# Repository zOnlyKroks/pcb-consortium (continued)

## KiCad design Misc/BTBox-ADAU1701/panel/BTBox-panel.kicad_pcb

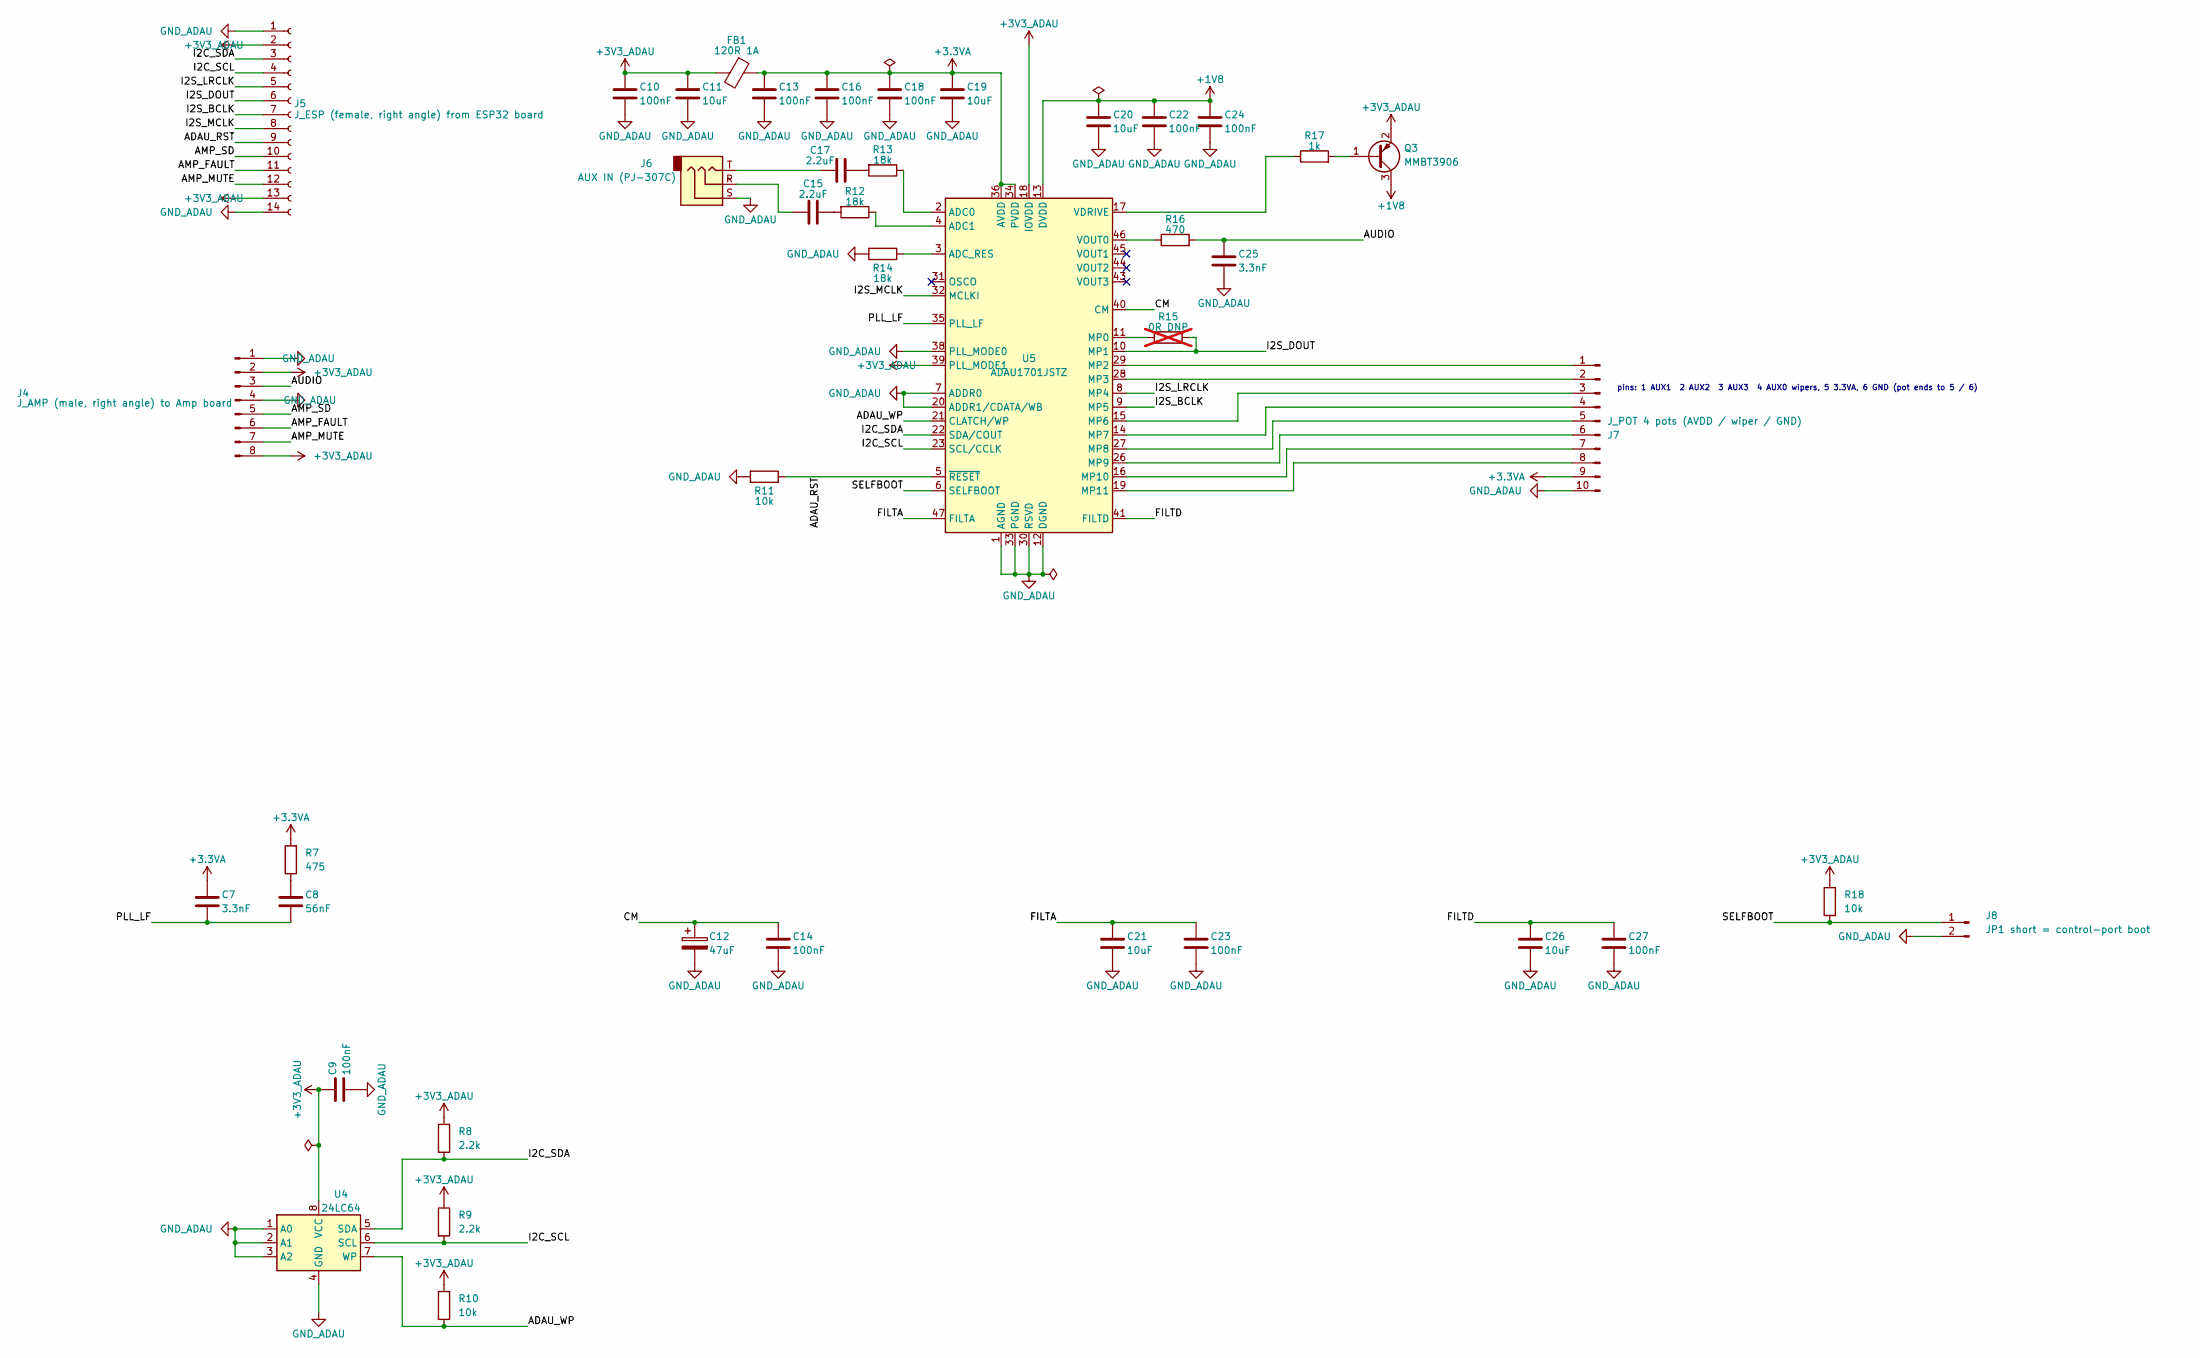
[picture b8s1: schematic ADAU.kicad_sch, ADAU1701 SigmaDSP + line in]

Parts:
C7, C25: 3.3nF; C_0603_1608Metric; LCSC Part # C1613
C8: 56nF; C_0603_1608Metric; LCSC Part # C282072
C9, C10, C13, C14, C16, C18, C22, C23, C24, C27: 100nF; C_0603_1608Metric; LCSC Part # C14663
C11, C19, C20, C21, C26: 10uF; C_0805_2012Metric; LCSC Part # C15850
C12: 47uF; CP_Elec_6.3x5.4; LCSC Part # C7469965
C15, C17: 2.2uF; C_0805_2012Metric; LCSC Part # C19110
FB1: 120R 1A; L_0805_2012Metric; LCSC Part # C356986
J4: J_AMP (male, right angle) to Amp board; PinHeader_1x08_P2.54mm_Horizontal
J5: J_ESP (female, right angle) from ESP32 board; PinSocket_1x14_P2.54mm_Horizontal
J6: AUX IN (PJ-307C); AUDIO-TH_PJ307C; LCSC Part # C16684
J7: J_POT 4 pots (AVDD / wiper / GND); PinSocket_1x10_P2.54mm_Vertical
J8: JP1 short = control-port boot; PinHeader_1x02_P2.54mm_Vertical; LCSC Part # C2894925
Q3: MMBT3906; SOT-23; LCSC Part # C53444
R7: 475; R_0603_1608Metric; LCSC Part # C23181
R8, R9: 2.2k; R_0603_1608Metric; LCSC Part # C4190
R10, R11, R18: 10k; R_0603_1608Metric; LCSC Part # C25804
R12, R13, R14: 18k; R_0603_1608Metric; LCSC Part # C100821
R15: 0R DNP; R_0603_1608Metric; LCSC Part # C21189; not fitted
R16: 470; R_0603_1608Metric; LCSC Part # C23179
R17: 1k; R_0603_1608Metric; LCSC Part # C21190
U4: 24LC64; SOIC-8_3.9x4.9mm_P1.27mm; LCSC Part # C5460
U5: ADAU1701JSTZ; LQFP-48_7x7mm_P0.5mm; LCSC Part # C3001875

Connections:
+1V8: C20.1, C22.1, C24.1, Q3.3 (C), U5.13 (DVDD), U5.24 (DVDD)
+3.3VA: C7.2, C13.1, C16.1, C18.1, C19.1, FB1.1, J7.9, R7.2, U5.34 (PVDD), U5.36 (AVDD), U5.48 (AVDD)
+3V3_ADAU: C9.1, C10.1, C11.1, FB1.2, J4.2, J4.8, J5.2, J5.13, Q3.2 (E), R8.1, R9.1, R10.1, R18.2, U4.8 (VCC), U5.18 (IOVDD), U5.39 (PLL_MODE1)
/ADAU/ADAU_RST: J5.9, R11.1, U5.5 (~RESET)
/ADAU/ADAU_WP: R10.2, U4.7 (WP), U5.21 (CLATCH/WP)
/ADAU/AMP_FAULT: J4.6, J5.11
/ADAU/AMP_MUTE: J4.7, J5.12
/ADAU/AMP_SD: J4.5, J5.10
/ADAU/AUDIO: C25.1, J4.3, R16.2
/ADAU/CM: C12.1, C14.1, U5.40 (CM)
/ADAU/FILTA: C21.1, C23.1, U5.47 (FILTA)
/ADAU/FILTD: C26.1, C27.1, U5.41 (FILTD)
/ADAU/I2C_SCL: J5.4, R9.2, U4.6 (SCL), U5.23 (SCL/CCLK)
/ADAU/I2C_SDA: J5.3, R8.2, U4.5 (SDA), U5.22 (SDA/COUT)
/ADAU/I2S_BCLK: J5.7, U5.9 (MP5)
/ADAU/I2S_DOUT: J5.6, R15.2, U5.10 (MP1)
/ADAU/I2S_LRCLK: J5.5, U5.8 (MP4)
/ADAU/I2S_MCLK: J5.8, U5.32 (MCLKI)
/ADAU/PLL_LF: C7.1, C8.1, U5.35 (PLL_LF)
/ADAU/SELFBOOT: J8.1, R18.1, U5.6 (SELFBOOT)
GND_ADAU: C9.2, C10.2, C11.2, C12.2, C13.2, C14.2, C16.2, C18.2, C19.2, C20.2, C21.2, C22.2, C23.2, C24.2, C25.2, C26.2, C27.2, J4.1, J4.4, J5.1, J5.14, J6.S, J7.10, J8.2, R11.2, R14.2, U4.1 (A0), U4.2 (A1), U4.3 (A2), U4.4 (GND), U5.1 (AGND), U5.7 (ADDR0), U5.12 (DGND), U5.20 (ADDR1/CDATA/WB), U5.25 (DGND), U5.30 (RSVD), U5.33 (PGND), U5.37 (AGND), U5.38 (PLL_MODE0), U5.42 (AGND)
unnamed: C8.2, R7.1
unnamed: C15.1, R12.2
unnamed: C15.2, J6.R
unnamed: C17.1, R13.2
unnamed: C17.2, J6.T
unnamed: J7.1, U5.29 (MP2)
unnamed: J7.2, U5.28 (MP3)
unnamed: J7.3, U5.15 (MP6)
unnamed: J7.4, U5.14 (MP7)
unnamed: J7.5, U5.27 (MP8)
unnamed: J7.6, U5.26 (MP9)
unnamed: J7.7, U5.16 (MP10)
unnamed: J7.8, U5.19 (MP11)
unnamed: Q3.1 (B), R17.2
unnamed: R13.1, U5.2 (ADC0)
unnamed: R12.1, U5.4 (ADC1)
unnamed: R14.1, U5.3 (ADC_RES)
unnamed: R15.1, U5.11 (MP0)
unnamed: R17.1, U5.17 (VDRIVE)
unnamed: R16.1, U5.46 (VOUT0)

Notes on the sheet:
pins: 1 AUX1 2 AUX2 3 AUX3 4 AUX0 wipers, 5 3.3VA, 6 GND (pot ends to 5 / 6)

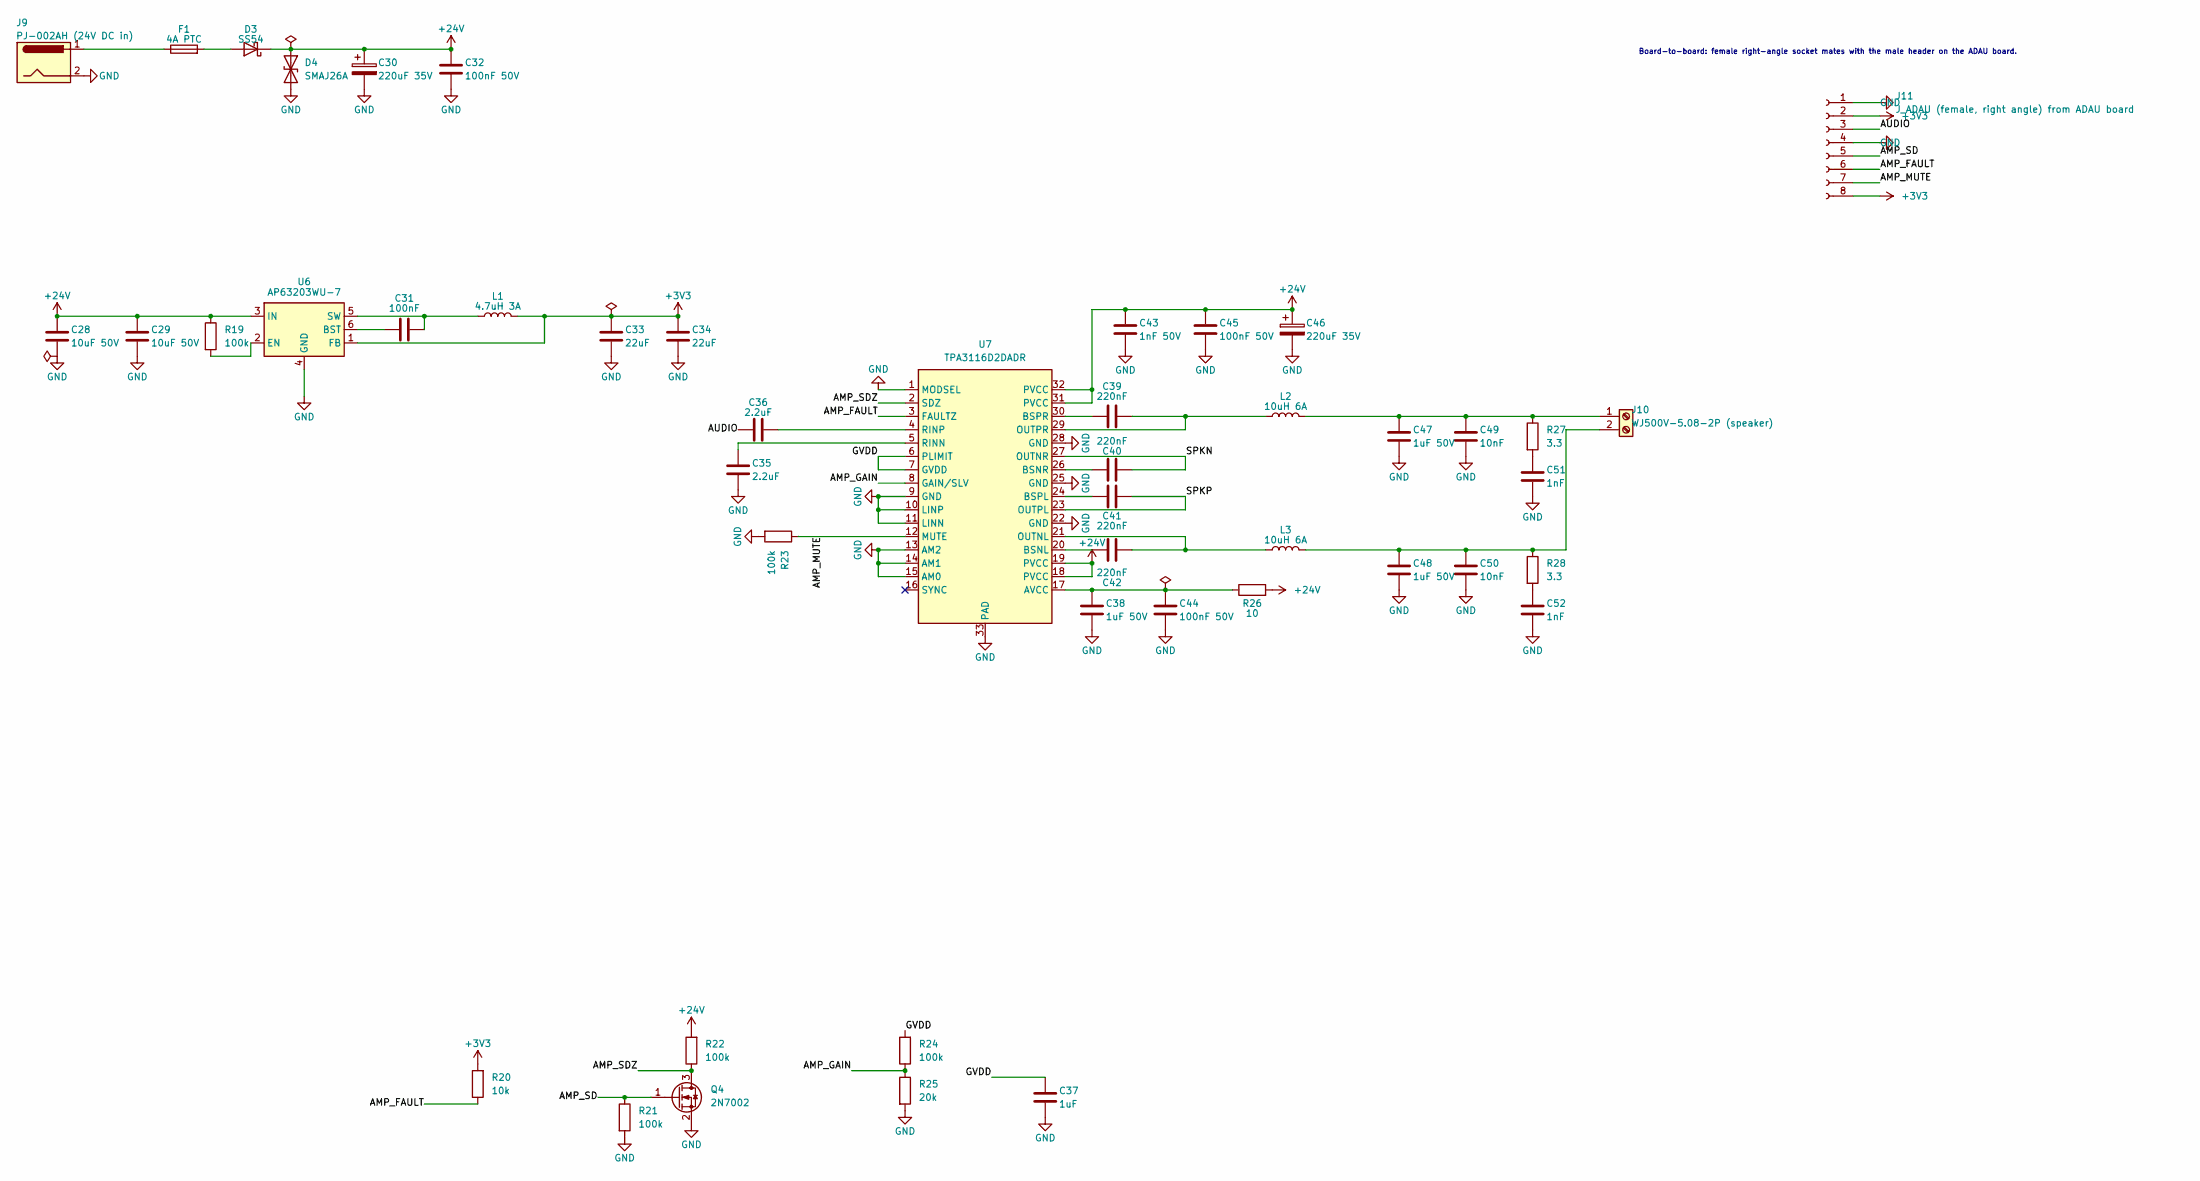
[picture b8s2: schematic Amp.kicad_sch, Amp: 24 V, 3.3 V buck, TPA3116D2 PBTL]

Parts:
C28, C29: 10uF 50V; C_1206_3216Metric; LCSC Part # C13585
C30, C46: 220uF 35V; CP_Elec_10x10.5; LCSC Part # C2886113
C31: 100nF; C_0603_1608Metric; LCSC Part # C14663
C32, C44, C45: 100nF 50V; C_0805_2012Metric; LCSC Part # C49678
C33, C34: 22uF; C_0805_2012Metric; LCSC Part # C45783
C35, C36: 2.2uF; C_0805_2012Metric; LCSC Part # C19110
C37: 1uF; C_0805_2012Metric; LCSC Part # C28323
C38, C47, C48: 1uF 50V; C_0805_2012Metric; LCSC Part # C91185
C39, C40, C41, C42: 220nF; C_0603_1608Metric; LCSC Part # C64705
C43: 1nF 50V; C_0603_1608Metric; LCSC Part # C1588
C49, C50: 10nF; C_0603_1608Metric; LCSC Part # C57112
C51, C52: 1nF; C_0603_1608Metric; LCSC Part # C1588
D3: SS54; D_SMA; LCSC Part # C22452
D4: SMAJ26A; D_SMA; LCSC Part # C148225
F1: 4A PTC; Fuse_1812_4532Metric
J9: PJ-002AH (24V DC in); BarrelJack_CUI_PJ-002AH; LCSC Part # C2961147
J10: WJ500V-5.08-2P (speaker); TerminalBlock_Phoenix_MKDS-1,5-2-5.08_1x02_P5.08mm_Horizont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; LCSC Part # C8465
J11: J_ADAU (female, right angle) from ADAU board; PinSocket_1x08_P2.54mm_Horizontal
L1: 4.7uH 3A; L_Bourns-SRN6028; LCSC Part # C168028
L2, L3: 10uH 6A; L_12x12mm_H8mm; LCSC Part # C2041557
Q4: 2N7002; SOT-23; LCSC Part # C8545
R19, R21, R22, R23, R24: 100k; R_0603_1608Metric; LCSC Part # C25803
R20: 10k; R_0603_1608Metric; LCSC Part # C25804
R25: 20k; R_0603_1608Metric; LCSC Part # C4184
R26: 10; R_0603_1608Metric; LCSC Part # C22859
R27, R28: 3.3; R_0603_1608Metric
U6: AP63203WU-7; TSOT-23-6; LCSC Part # C780769
U7: TPA3116D2DADR; HTSSOP-32_L11.0-W6.1-P0.65-LS8.1-BL; LCSC Part # C50144

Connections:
+3V3: C33.1, C34.1, J11.2, J11.8, L1.2, R20.2, U6.1 (FB)
+24V: C28.1, C29.1, C30.1, C32.1, C43.1, C45.1, C46.1, D3.1 (K), D4.1 (A1), R19.1, R22.2, R26.2, U6.3 (IN), U7.18 (PVCC), U7.19 (PVCC), U7.31 (PVCC), U7.32 (PVCC)
/Amp/AMP_FAULT: J11.6, R20.1, U7.3 (FAULTZ)
/Amp/AMP_GAIN: R24.1, R25.1, U7.8 (GAIN/SLV)
/Amp/AMP_MUTE: J11.7, R23.1, U7.12 (MUTE)
/Amp/AMP_SD: J11.5, Q4.1 (G), R21.1
/Amp/AMP_SDZ: Q4.3 (D), R22.1, U7.2 (SDZ)
/Amp/AUDIO: C36.1, J11.3
/Amp/GVDD: C37.1, R24.2, U7.6 (PLIMIT), U7.7 (GVDD)
/Amp/SPKN: C40.1, U7.27 (OUTNR)
/Amp/SPKP: C41.2, U7.23 (OUTPL)
GND: C28.2, C29.2, C30.2, C32.2, C33.2, C34.2, C35.2, C37.2, C38.2, C43.2, C44.2, C45.2, C46.2, C47.2, C48.2, C49.2, C50.2, C51.2, C52.2, D4.2 (A2), J9.2, J11.1, J11.4, Q4.2 (S), R21.2, R23.2, R25.2, U6.4 (GND), U7.1 (MODSEL), U7.9 (GND), U7.10 (LINP), U7.11 (LINN), U7.13 (AM2), U7.14 (AM1), U7.15 (AM0), U7.22 (GND), U7.25 (GND), U7.28 (GND), U7.33 (PAD)
unnamed: C51.1, R27.2
unnamed: C52.1, R28.2
unnamed: D3.2 (A), F1.2
unnamed: F1.1, J9.1
unnamed: C47.1, C49.1, J10.1, L2.2, R27.1
unnamed: C48.1, C50.1, J10.2, L3.2, R28.1
unnamed: C31.1, U6.6 (BST)
unnamed: R19.2, U6.2 (EN)
unnamed: C31.2, L1.1, U6.5 (SW)
unnamed: C38.1, C44.1, R26.1, U7.17 (AVCC)
unnamed: C42.2, U7.20 (BSNL)
unnamed: C40.2, U7.26 (BSNR)
unnamed: C41.1, U7.24 (BSPL)
unnamed: C39.1, U7.30 (BSPR)
unnamed: C42.1, L3.1, U7.21 (OUTNL)
unnamed: C39.2, L2.1, U7.29 (OUTPR)
unnamed: C35.1, U7.5 (RINN)
unnamed: C36.2, U7.4 (RINP)

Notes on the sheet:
Board-to-board: female right-angle socket mates with the male header on the ADAU board.

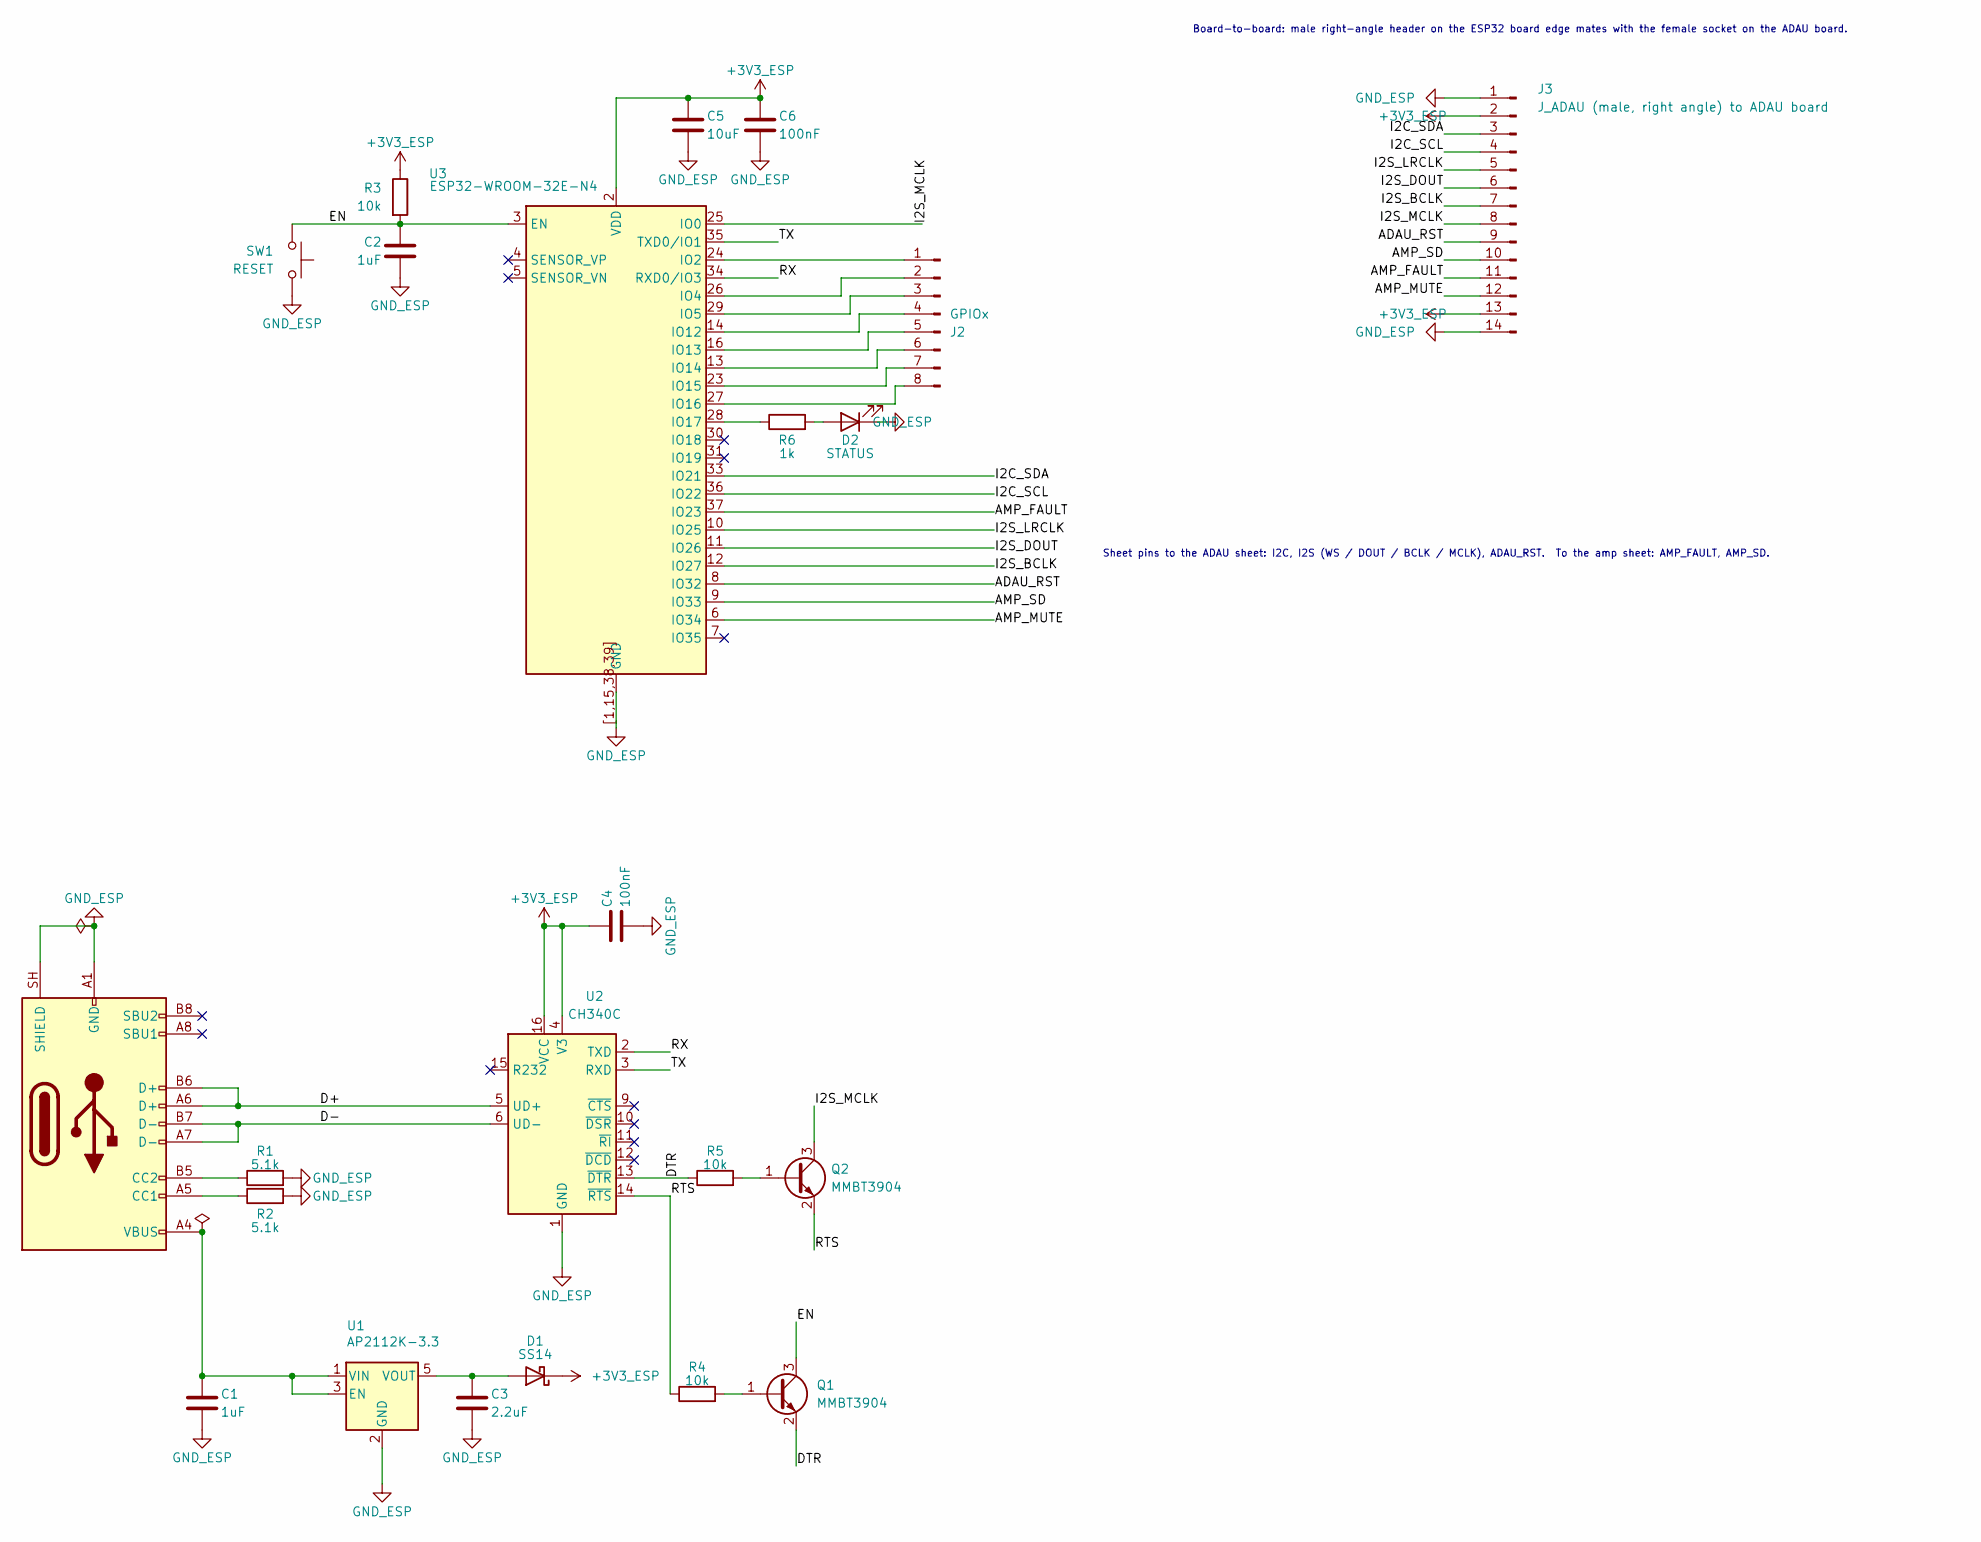
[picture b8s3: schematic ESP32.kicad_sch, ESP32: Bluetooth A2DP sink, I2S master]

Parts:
C1: 1uF; C_0805_2012Metric; LCSC Part # C28323
C2: 1uF; C_0603_1608Metric; LCSC Part # C15849
C3: 2.2uF; C_0805_2012Metric; LCSC Part # C19110
C4, C6: 100nF; C_0603_1608Metric; LCSC Part # C14663
C5: 10uF; C_0805_2012Metric; LCSC Part # C15850
D1: SS14; D_SMA; LCSC Part # C2480
D2: STATUS; LED_0603_1608Metric; LCSC Part # C2286
J1: USB-C (flash / console); USB_C_Receptacle_HRO_TYPE-C-31-M-12; LCSC Part # C165948
J2: GPIOx; PinSocket_1x08_P2.54mm_Vertical
J3: J_ADAU (male, right angle) to ADAU board; PinHeader_1x14_P2.54mm_Horizontal
Q1, Q2: MMBT3904; SOT-23; LCSC Part # C20526
R1, R2: 5.1k; R_0603_1608Metric; LCSC Part # C23186
R3, R4, R5: 10k; R_0603_1608Metric; LCSC Part # C25804
R6: 1k; R_0603_1608Metric; LCSC Part # C21190
SW1: RESET; SW_Push_1P1T_NO_CK_KMR2; LCSC Part # C72443
U1: AP2112K-3.3; SOT-23-5; LCSC Part # C51118
U2: CH340C; SOIC-16_3.9x9.9mm_P1.27mm; LCSC Part # C84681
U3: ESP32-WROOM-32E-N4; ESP32-WROOM-32E; LCSC Part # C701341

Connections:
+3V3_ESP: C4.1, C5.1, C6.1, D1.1 (K), J3.2, J3.13, R3.1, U2.4 (V3), U2.16 (VCC), U3.2 (VDD)
/ESP32/ADAU_RST: J3.9, U3.8 (IO32)
/ESP32/AMP_FAULT: J3.11, U3.37 (IO23)
/ESP32/AMP_MUTE: J3.12, U3.6 (IO34)
/ESP32/AMP_SD: J3.10, U3.9 (IO33)
/ESP32/D+: J1.A6 (D+), J1.B6 (D+), U2.5 (UD+)
/ESP32/D-: J1.A7 (D-), J1.B7 (D-), U2.6 (UD-)
/ESP32/DTR: Q1.2 (E), R5.1, U2.13 (~DTR)
/ESP32/EN: C2.1, Q1.3 (C), R3.2, SW1.1, U3.3 (EN)
/ESP32/I2C_SCL: J3.4, U3.36 (IO22)
/ESP32/I2C_SDA: J3.3, U3.33 (IO21)
/ESP32/I2S_BCLK: J3.7, U3.12 (IO27)
/ESP32/I2S_DOUT: J3.6, U3.11 (IO26)
/ESP32/I2S_LRCLK: J3.5, U3.10 (IO25)
/ESP32/I2S_MCLK: J3.8, Q2.3 (C), U3.25 (IO0)
/ESP32/RTS: Q2.2 (E), R4.1, U2.14 (~RTS)
/ESP32/RX: U2.2 (TXD), U3.34 (RXD0/IO3)
/ESP32/TX: U2.3 (RXD), U3.35 (TXD0/IO1)
GND_ESP: C1.2, C2.2, C3.2, C4.2, C5.2, C6.2, D2.1 (K), J1.A1 (GND), J1.A12 (GND), J1.B1 (GND), J1.B12 (GND), J1.SH (SHIELD), J3.1, J3.14, R1.2, R2.2, SW1.2, U1.2 (GND), U2.1 (GND), U3.1 (GND), U3.15 (GND), U3.38 (GND), U3.39 (GND), U3.[1,15,38,39] (GND)
unnamed: C3.1, D1.2 (A), U1.5 (VOUT)
unnamed: D2.2 (A), R6.2
unnamed: J1.A5 (CC1), R2.1
unnamed: J1.B5 (CC2), R1.1
unnamed: J2.1, U3.24 (IO2)
unnamed: J2.2, U3.26 (IO4)
unnamed: J2.3, U3.29 (IO5)
unnamed: J2.4, U3.14 (IO12)
unnamed: J2.5, U3.16 (IO13)
unnamed: J2.6, U3.13 (IO14)
unnamed: J2.7, U3.23 (IO15)
unnamed: J2.8, U3.27 (IO16)
unnamed: Q1.1 (B), R4.2
unnamed: Q2.1 (B), R5.2
unnamed: C1.1, J1.A4 (VBUS), J1.A9 (VBUS), J1.B4 (VBUS), J1.B9 (VBUS), U1.1 (VIN), U1.3 (EN)
unnamed: R6.1, U3.28 (IO17)

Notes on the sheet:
Board-to-board: male right-angle header on the ESP32 board edge mates with the female socket on the ADAU board.
Sheet pins to the ADAU sheet: I2C, I2S (WS / DOUT / BCLK / MCLK), ADAU_RST. To the amp sheet: AMP_FAULT, AMP_SD.

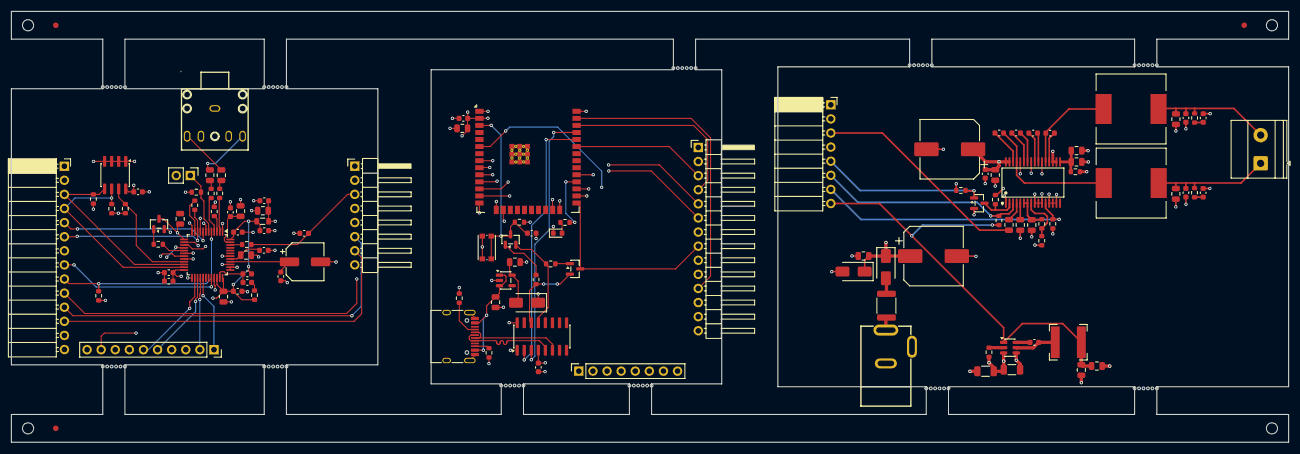
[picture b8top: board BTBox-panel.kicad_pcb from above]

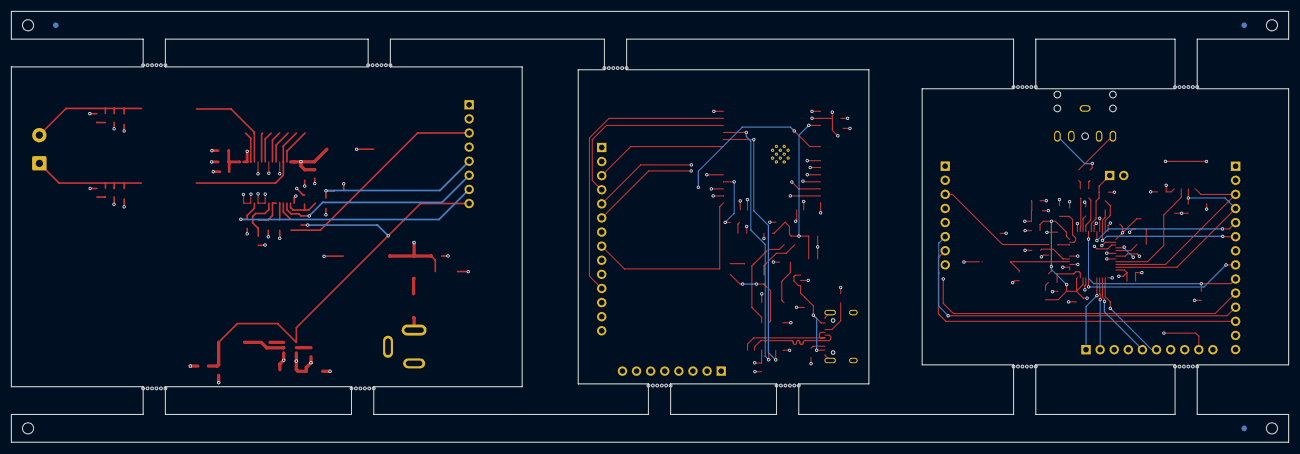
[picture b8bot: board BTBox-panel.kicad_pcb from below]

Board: 4 copper layers, 230.0 x 77.6 mm, 188 parts (3 on the bottom side), 106 nets.

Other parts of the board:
KiKit_FID_B_1, KiKit_FID_B_2, KiKit_FID_B_3: Fiducial
KiKit_FID_T_1, KiKit_FID_T_2, KiKit_FID_T_3: Fiducial
KiKit_MB_1_1, KiKit_MB_1_2, KiKit_MB_1_3, KiKit_MB_1_4, KiKit_MB_1_5, KiKit_MB_1_6, KiKit_MB_2_1, KiKit_MB_2_2, KiKit_MB_2_3, KiKit_MB_2_4, KiKit_MB_2_5, KiKit_MB_2_6, KiKit_MB_3_1, KiKit_MB_3_2, KiKit_MB_3_3, KiKit_MB_3_4, KiKit_MB_3_5, KiKit_MB_3_6, KiKit_MB_4_1, KiKit_MB_4_2, KiKit_MB_4_3, KiKit_MB_4_4, KiKit_MB_4_5, KiKit_MB_4_6, KiKit_MB_5_1, KiKit_MB_5_2, KiKit_MB_5_3, KiKit_MB_5_4, KiKit_MB_5_5, KiKit_MB_5_6, KiKit_MB_6_1, KiKit_MB_6_2, KiKit_MB_6_3, KiKit_MB_6_4, KiKit_MB_6_5, KiKit_MB_6_6, KiKit_MB_7_1, KiKit_MB_7_2, KiKit_MB_7_3, KiKit_MB_7_4, KiKit_MB_7_5, KiKit_MB_7_6, KiKit_MB_8_1, KiKit_MB_8_2, KiKit_MB_8_3, KiKit_MB_8_4, KiKit_MB_8_5, KiKit_MB_8_6, KiKit_MB_9_1, KiKit_MB_9_2, KiKit_MB_9_3, KiKit_MB_9_4, KiKit_MB_9_5, KiKit_MB_9_6, KiKit_MB_10_1, KiKit_MB_10_2, KiKit_MB_10_3, KiKit_MB_10_4, KiKit_MB_10_5, KiKit_MB_10_6, KiKit_MB_11_1, KiKit_MB_11_2, KiKit_MB_11_3, KiKit_MB_11_4, KiKit_MB_11_5, KiKit_MB_11_6: NPTH
KiKit_TO_1, KiKit_TO_2, KiKit_TO_3, KiKit_TO_4: NPTH

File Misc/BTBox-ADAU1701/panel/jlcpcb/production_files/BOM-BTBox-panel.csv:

Comment,Designator,Footprint,LCSC,Quantity
10,R26,R_0603_1608Metric,C22859,1
100k,"R19,R21,R22,R23,R24",R_0603_1608Metric,C25803,5
100nF,"C10,C13,C14,C16,C18,C22,C23,C24,C27,C31,C4,C6,C9",C_0603_1608Metric,C14663,13
100nF 50V,"C32,C44,C45",C_0805_2012Metric,C49678,3
10k,"R10,R11,R18,R20,R3,R4,R5",R_0603_1608Metric,C25804,7
10nF,"C49,C50",C_0603_1608Metric,C57112,2
10uF,"C11,C19,C20,C21,C26,C5",C_0805_2012Metric,C15850,6
10uF 50V,"C28,C29",C_1206_3216Metric,C13585,2
10uH 6A,"L2,L3",L_12x12mm_H8mm,C2041557,2
120R 1A,FB1,L_0805_2012Metric,C356986,1
18k,"R12,R13,R14",R_0603_1608Metric,C100821,3
1k,"R17,R6",R_0603_1608Metric,C21190,2
1nF,"C51,C52",C_0603_1608Metric,C1588,2
1nF 50V,C43,C_0603_1608Metric,C1588,1
1uF,C2,C_0603_1608Metric,C15849,1
1uF,"C1,C37",C_0805_2012Metric,C28323,2
1uF 50V,"C38,C47,C48",C_0805_2012Metric,C91185,3
2.2k,"R8,R9",R_0603_1608Metric,C4190,2
2.2uF,"C15,C17,C35,C36",C_0805_2012Metric,C19110,4
2.2uF,C3,C_0805_2012Metric,C377773,1
20k,R25,R_0603_1608Metric,C4184,1
220nF,"C39,C40,C41,C42",C_0603_1608Metric,C64705,4
220uF 35V,"C30,C46",CP_Elec_10x10.5,C2886113,2
22uF,"C33,C34",C_0805_2012Metric,C45783,2
24LC64,U4,SOIC-8_3.9x4.9mm_P1.27mm,C5460,1
2N7002,Q4,SOT-23,C8545,1
3.3nF,"C25,C7",C_0603_1608Metric,C1613,2
4.7uH 3A,L1,L_Bourns-SRN6028,C168028,1
470,R16,R_0603_1608Metric,C23179,1
475,R7,R_0603_1608Metric,C23181,1
47uF,C12,CP_Elec_6.3x5.4,C7469965,1
4A PTC,F1,Fuse_1812_4532Metric,C2982282,1
5.1k,"R1,R2",R_0603_1608Metric,C23186,2
56nF,C8,C_0603_1608Metric,C282072,1
ADAU1701JSTZ,U5,LQFP-48_7x7mm_P0.5mm,C3001875,1
AP2112K-3.3,U1,SOT-23-5,C51118,1
AP63203WU-7,U6,TSOT-23-6,C780769,1
AUX IN (PJ-307C),J6,AUDIO-TH_PJ307C,C16684,1
CH340C,U2,SOIC-16_3.9x9.9mm_P1.27mm,C84681,1
ESP32-WROOM-32E-N4,U3,ESP32-WROOM-32E,C701341,1
JP1 short = control-port boot,J8,PinHeader_1x02_P2.54mm_Vertical,C2894925,1
MMBT3904,"Q1,Q2",SOT-23,C20526,2
MMBT3906,Q3,SOT-23,C53444,1
PJ-002AH (24V DC in),J9,BarrelJack_CUI_PJ-002AH,C2961147,1
RESET,SW1,SW_Push_1P1T_NO_CK_KMR2,C72443,1
SMAJ26A,D4,D_SMA,C148225,1
SS14,D1,D_SMA,C2480,1
SS54,D3,D_SMA,C22452,1
STATUS,D2,LED_0603_1608Metric,C2286,1
TPA3116D2DADR,U7,HTSSOP-32_L11.0-W6.1-P0.65-LS8.1-BL,C50144,1
USB-C (flash / console),J1,USB_C_Receptacle_HRO_TYPE-C-31-M-12,C165948,1
WJ500V-5.08-2P (speaker),J10,"TerminalBlock_Phoenix_MKDS-1,5-2-5.08_1x02_P5.08mm_Horizontal",C8465,1
3.3,R28,R_0603_1608Metric,,1
3.3,R27,R_0603_1608Metric,,1
GPIOx,J2,PinSocket_1x08_P2.54mm_Vertical,,1
J_POT 4 pots (AVDD / wiper / GND),J7,PinSocket_1x10_P2.54mm_Vertical,,1
"J_ADAU (male, right angle) to ADAU board",J3,PinHeader_1x14_P2.54mm_Horizontal,,1
"J_AMP (male, right angle) to Amp board",J4,PinHeader_1x08_P2.54mm_Horizontal,,1
"J_ADAU (female, right angle) from ADAU board",J11,PinSocket_1x08_P2.54mm_Horizontal,,1
"J_ESP (female, right angle) from ESP32 board",J5,PinSocket_1x14_P2.54mm_Horizontal,,1
